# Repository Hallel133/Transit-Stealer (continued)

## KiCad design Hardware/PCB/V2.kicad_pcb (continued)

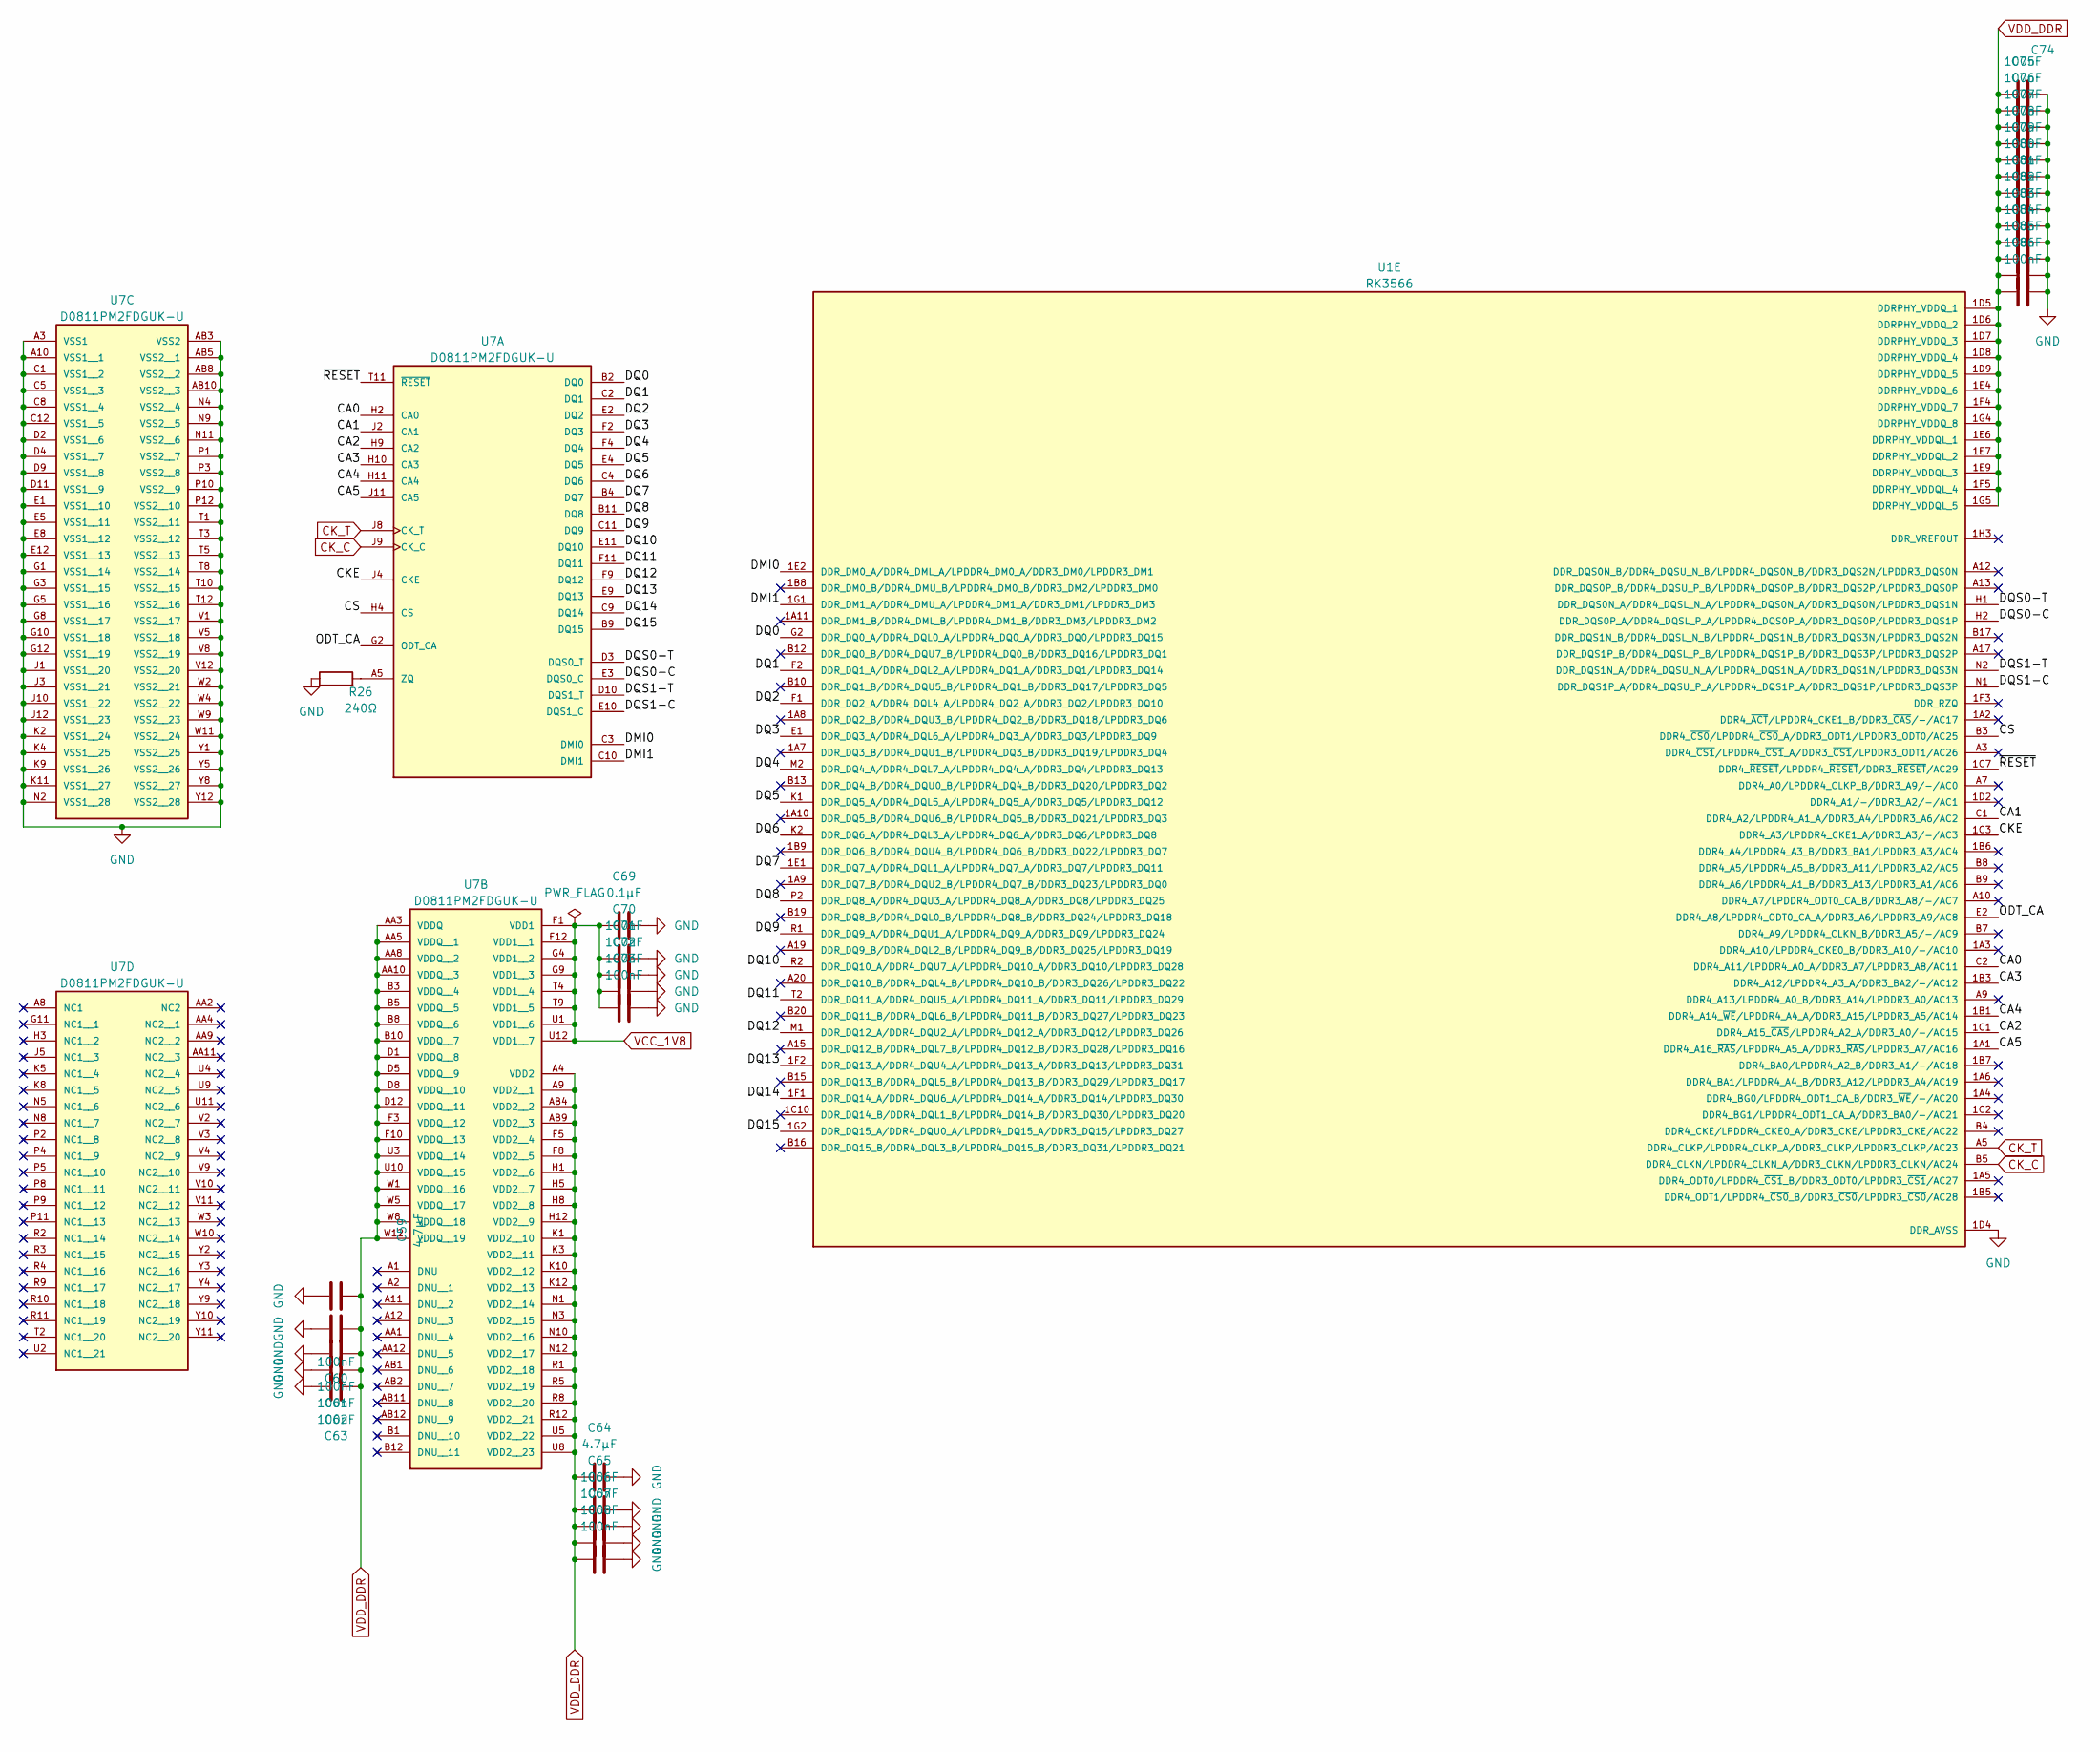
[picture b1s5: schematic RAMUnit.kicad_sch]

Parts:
C59, C64: 4.7µF; C_0402_1005Metric
C60, C61, C62, C63, C65, C66, C67, C68, C70, C71, C72, C73, C74, C75, C76, C77, C78, C79, C80, C81, C82, C83, C84, C85, C86: 100nF; C_0402_1005Metric
C69: 0.1µF; C_0402_1005Metric
R26: 240Ω; R_0402_1005Metric_Pad0.72x0.64mm_HandSolder
U1: RK3566; PARTREV 1.1
U7: D0811PM2FDGUK-U; PARTREV A00

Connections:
/LPDDR4/CA0: U1.C2 (DDR4_A11/LPDDR4_A0_A/DDR3_A7/LPDDR3_A8/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), U7.H2 (CA0)
/LPDDR4/CA1: U1.C1 (DDR4_A2/LPDDR4_A1_A/DDR3_A4/LPDDR3_A6/A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), U7.J2 (CA1)
/LPDDR4/CA2: U1.1C1 (DDR4_A15_~CAS/LPDDR4_A2_A/DDR3_A0/-/AC15), U7.H9 (CA2)
/LPDDR4/CA3: U1.1B3 (DDR4_A12/LPDDR4_A3_A/DDR3_BA2/-/AC12), U7.H10 (CA3)
/LPDDR4/CA4: U1.1B1 (DDR4_A14_~WE/LPDDR4_A4_A/DDR3_A15/LPDDR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), U7.H11 (CA4)
/LPDDR4/CA5: U1.1A1 (DDR4_A16_~RAS/LPDDR4_A5_A/DDR3_~RAS/LPD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), U7.J11 (CA5)
/LPDDR4/CKE: U1.1C3 (DDR4_A3/LPDDR4_CKE1_A/DDR3_A3/-/AC3), U7.J4 (CKE)
/LPDDR4/CS: U1.B3 (DDR4_~CS0/LPDDR4_~CS0_A/DDR3_ODT1/LPDDR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), U7.H4 (CS)
/LPDDR4/DMI0: U1.1E2 (DDR_DM0_A/DDR4_DML_A/LPDDR4_DM0_A/DDR3_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), U7.C3 (DMI0)
/LPDDR4/DMI1: U1.1G1 (DDR_DM1_A/DDR4_DMU_A/LPDDR4_DM1_A/DDR3_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), U7.C10 (DMI1)
/LPDDR4/DQ0: U1.G2 (DDR_DQ0_A/DDR4_DQL0_A/LPDDR4_DQ0_A/DDR3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), U7.B2 (DQ0)
/LPDDR4/DQ1: U1.F2 (DDR_DQ1_A/DDR4_DQL2_A/LPDDR4_DQ1_A/DDR3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), U7.C2 (DQ1)
/LPDDR4/DQ2: U1.F1 (DDR_DQ2_A/DDR4_DQL4_A/LPDDR4_DQ2_A/DDR3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), U7.E2 (DQ2)
/LPDDR4/DQ3: U1.E1 (DDR_DQ3_A/DDR4_DQL6_A/LPDDR4_DQ3_A/DDR3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), U7.F2 (DQ3)
/LPDDR4/DQ4: U1.M2 (DDR_DQ4_A/DDR4_DQL7_A/LPDDR4_DQ4_A/DDR3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), U7.F4 (DQ4)
/LPDDR4/DQ5: U1.K1 (DDR_DQ5_A/DDR4_DQL5_A/LPDDR4_DQ5_A/DDR3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), U7.E4 (DQ5)
/LPDDR4/DQ6: U1.K2 (DDR_DQ6_A/DDR4_DQL3_A/LPDDR4_DQ6_A/DDR3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), U7.C4 (DQ6)
/LPDDR4/DQ7: U1.1E1 (DDR_DQ7_A/DDR4_DQL1_A/LPDDR4_DQ7_A/DDR3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), U7.B4 (DQ7)
/LPDDR4/DQ8: U1.P2 (DDR_DQ8_A/DDR4_DQU3_A/LPDDR4_DQ8_A/DDR3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), U7.B11 (DQ8)
/LPDDR4/DQ9: U1.R1 (DDR_DQ9_A/DDR4_DQU1_A/LPDDR4_DQ9_A/DDR3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), U7.C11 (DQ9)
/LPDDR4/DQ10: U1.R2 (DDR_DQ10_A/DDR4_DQU7_A/LPDDR4_DQ10_A/DD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), U7.E11 (DQ10)
/LPDDR4/DQ11: U1.T2 (DDR_DQ11_A/DDR4_DQU5_A/LPDDR4_DQ11_A/DD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), U7.F11 (DQ11)
/LPDDR4/DQ12: U1.M1 (DDR_DQ12_A/DDR4_DQU2_A/LPDDR4_DQ12_A/DD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), U7.F9 (DQ12)
/LPDDR4/DQ13: U1.1F2 (DDR_DQ13_A/DDR4_DQU4_A/LPDDR4_DQ13_A/DD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), U7.E9 (DQ13)
/LPDDR4/DQ14: U1.1F1 (DDR_DQ14_A/DDR4_DQU6_A/LPDDR4_DQ14_A/DD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), U7.C9 (DQ14)
/LPDDR4/DQ15: U1.1G2 (DDR_DQ15_A/DDR4_DQU0_A/LPDDR4_DQ15_A/DD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), U7.B9 (DQ15)
/LPDDR4/DQS0-C: U1.H2 (DDR_DQS0P_A/DDR4_DQSL_P_A/LPDDR4_DQS0P_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), U7.E3 (DQS0_C)
/LPDDR4/DQS0-T: U1.H1 (DDR_DQS0N_A/DDR4_DQSL_N_A/LPDDR4_DQS0N_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), U7.D3 (DQS0_T)
/LPDDR4/DQS1-C: U1.N1 (DDR_DQS1P_A/DDR4_DQSU_P_A/LPDDR4_DQS1P_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), U7.E10 (DQS1_C)
/LPDDR4/DQS1-T: U1.N2 (DDR_DQS1N_A/DDR4_DQSU_N_A/LPDDR4_DQS1N_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), U7.D10 (DQS1_T)
/LPDDR4/ODT_CA: U1.E2 (DDR4_A8/LPDDR4_ODT0_CA_A/DDR3_A6/LPDDR3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), U7.G2 (ODT_CA)
/LPDDR4/~RESET: U1.1C7 (DDR4_~RESET/LPDDR4_~RESET/DDR3_~RESET/A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), U7.T11 (~RESET)
CK_C: U1.B5 (DDR4_CLKN/LPDDR4_CLKN_A/DDR3_CLKN/LPDDR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), U7.J9 (CK_C)
CK_T: U1.A5 (DDR4_CLKP/LPDDR4_CLKP_A/DDR3_CLKP/LPDDR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), U7.J8 (CK_T)
GND: C59.2, C60.2, C61.2, C62.2, C63.2, C64.2, C65.2, C66.2, C67.2, C68.2, C69.1, C70.2, C71.2, C72.2, C73.2, C74.2, C75.2, C76.2, C77.2, C78.2, C79.2, C80.2, C81.2, C82.2, C83.2, C84.2, C85.2, C86.2, R26.1, U1.1D4 (DDR_AVSS), U7.A3 (VSS1), U7.A10 (VSS1__1), U7.AB3 (VSS2), U7.AB5 (VSS2__1), U7.AB8 (VSS2__2), U7.AB10 (VSS2__3), U7.C1 (VSS1__2), U7.C5 (VSS1__3), U7.C8 (VSS1__4), U7.C12 (VSS1__5), U7.D2 (VSS1__6), U7.D4 (VSS1__7), U7.D9 (VSS1__8), U7.D11 (VSS1__9), U7.E1 (VSS1__10), U7.E5 (VSS1__11), U7.E8 (VSS1__12), U7.E12 (VSS1__13), U7.G1 (VSS1__14), U7.G3 (VSS1__15), U7.G5 (VSS1__16), U7.G8 (VSS1__17), U7.G10 (VSS1__18), U7.G12 (VSS1__19), U7.J1 (VSS1__20), U7.J3 (VSS1__21), U7.J10 (VSS1__22), U7.J12 (VSS1__23), U7.K2 (VSS1__24), U7.K4 (VSS1__25), U7.K9 (VSS1__26), U7.K11 (VSS1__27), U7.N2 (VSS1__28), U7.N4 (VSS2__4), U7.N9 (VSS2__5), U7.N11 (VSS2__6), U7.P1 (VSS2__7), U7.P3 (VSS2__8), U7.P10 (VSS2__9), U7.P12 (VSS2__10), U7.T1 (VSS2__11), U7.T3 (VSS2__12), U7.T5 (VSS2__13), U7.T8 (VSS2__14), U7.T10 (VSS2__15), U7.T12 (VSS2__16), U7.V1 (VSS2__17), U7.V5 (VSS2__18), U7.V8 (VSS2__19), U7.V12 (VSS2__20), U7.W2 (VSS2__21), U7.W4 (VSS2__22), U7.W9 (VSS2__23), U7.W11 (VSS2__24), U7.Y1 (VSS2__25), U7.Y5 (VSS2__26), U7.Y8 (VSS2__27), U7.Y12 (VSS2__28); also elsewhere on the board
unnamed: R26.2, U7.A5 (ZQ)
VCC_1V8: C69.2, C70.1, C71.1, C72.1, C73.1, U7.F1 (VDD1), U7.F12 (VDD1__1), U7.G4 (VDD1__2), U7.G9 (VDD1__3), U7.T4 (VDD1__4), U7.T9 (VDD1__5), U7.U1 (VDD1__6), U7.U12 (VDD1__7); also elsewhere on the board
VDD_DDR: C59.1, C60.1, C61.1, C62.1, C63.1, C64.1, C65.1, C66.1, C67.1, C68.1, C74.1, C75.1, C76.1, C77.1, C78.1, C79.1, C80.1, C81.1, C82.1, C83.1, C84.1, C85.1, C86.1, U1.1D5 (DDRPHY_VDDQ_1), U1.1D6 (DDRPHY_VDDQ_2), U1.1D7 (DDRPHY_VDDQ_3), U1.1D8 (DDRPHY_VDDQ_4), U1.1D9 (DDRPHY_VDDQ_5), U1.1E4 (DDRPHY_VDDQ_6), U1.1E6 (DDRPHY_VDDQL_1), U1.1E7 (DDRPHY_VDDQL_2), U1.1E9 (DDRPHY_VDDQL_3), U1.1F4 (DDRPHY_VDDQ_7), U1.1F5 (DDRPHY_VDDQL_4), U1.1G4 (DDRPHY_VDDQ_8), U1.1G5 (DDRPHY_VDDQL_5), U7.A4 (VDD2), U7.A9 (VDD2__1), U7.AA3 (VDDQ), U7.AA5 (VDDQ__1), U7.AA8 (VDDQ__2), U7.AA10 (VDDQ__3), U7.AB4 (VDD2__2), U7.AB9 (VDD2__3), U7.B3 (VDDQ__4), U7.B5 (VDDQ__5), U7.B8 (VDDQ__6), U7.B10 (VDDQ__7), U7.D1 (VDDQ__8), U7.D5 (VDDQ__9), U7.D8 (VDDQ__10), U7.D12 (VDDQ__11), U7.F3 (VDDQ__12), U7.F5 (VDD2__4), U7.F8 (VDD2__5), U7.F10 (VDDQ__13), U7.H1 (VDD2__6), U7.H5 (VDD2__7), U7.H8 (VDD2__8), U7.H12 (VDD2__9), U7.K1 (VDD2__10), U7.K3 (VDD2__11), U7.K10 (VDD2__12), U7.K12 (VDD2__13), U7.N1 (VDD2__14), U7.N3 (VDD2__15), U7.N10 (VDD2__16), U7.N12 (VDD2__17), U7.R1 (VDD2__18), U7.R5 (VDD2__19), U7.R8 (VDD2__20), U7.R12 (VDD2__21), U7.U3 (VDDQ__14), U7.U5 (VDD2__22), U7.U8 (VDD2__23), U7.U10 (VDDQ__15), U7.W1 (VDDQ__16), U7.W5 (VDDQ__17), U7.W8 (VDDQ__18), U7.W12 (VDDQ__19); also elsewhere on the board

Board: 8 copper layers, 158 parts (35 on the bottom side), 163 nets, no tracks yet.

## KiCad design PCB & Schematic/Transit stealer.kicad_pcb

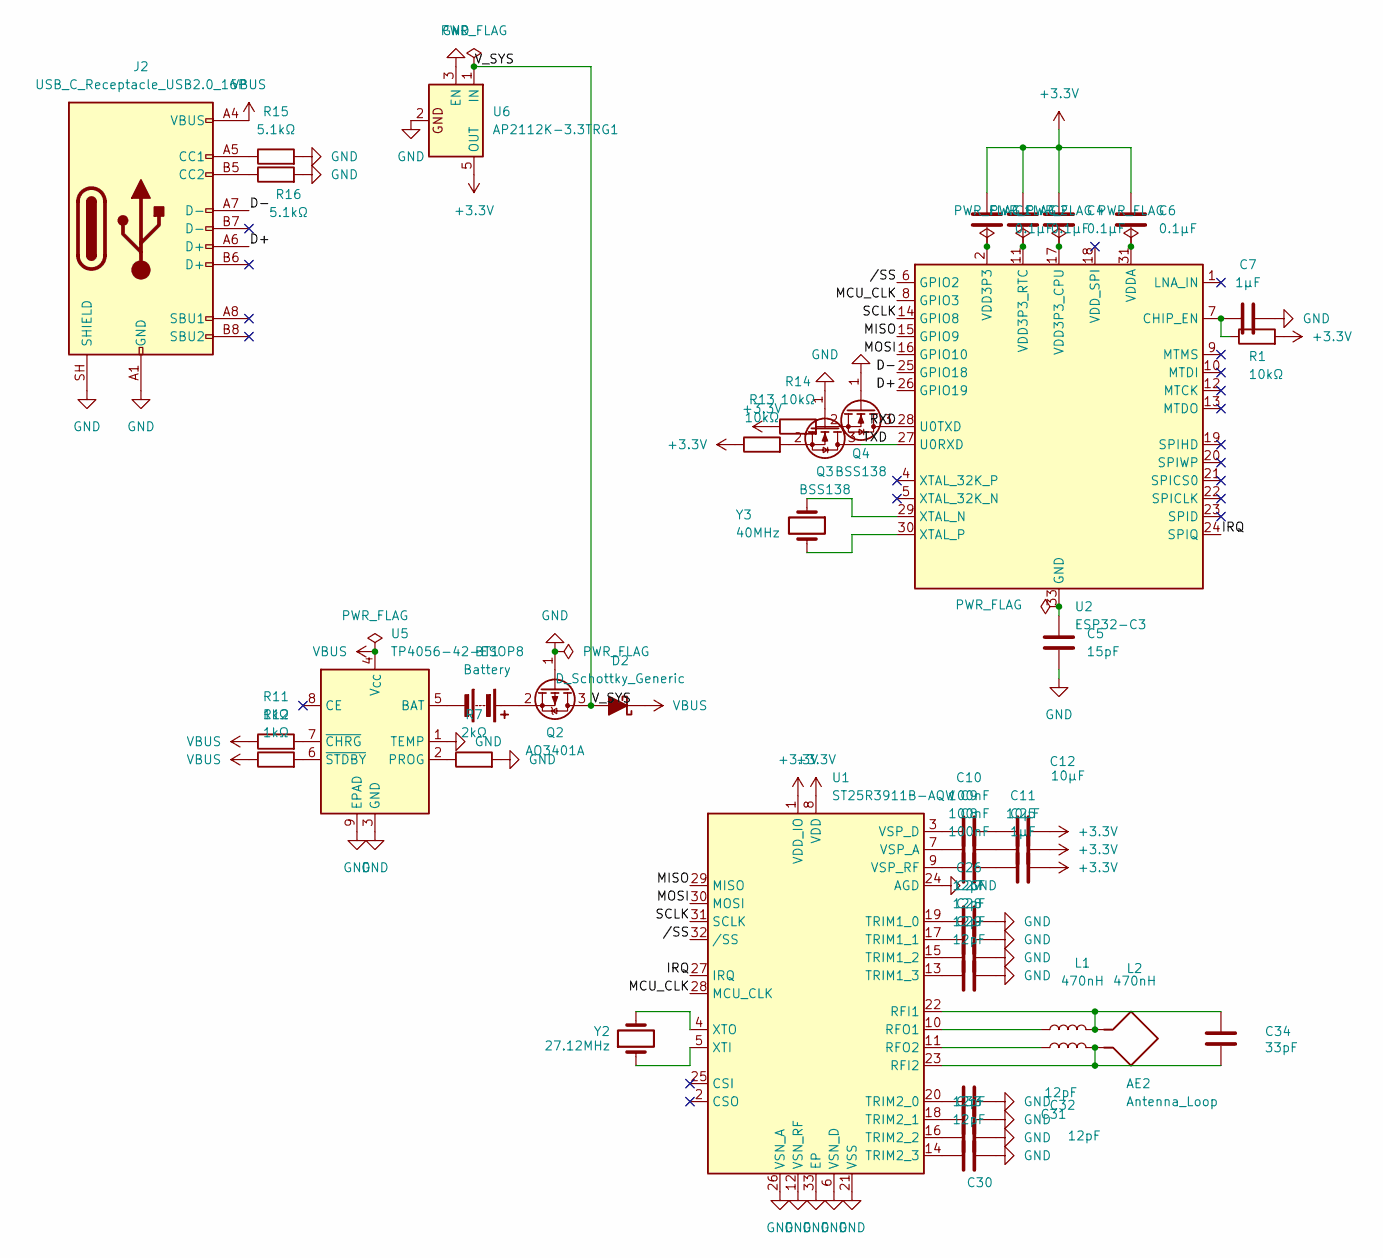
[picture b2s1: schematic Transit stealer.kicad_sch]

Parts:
AE2: Antenna_Loop; NFC Antenna
BT1: Battery; SolderWire-0.127sqmm_1x02_P3.7mm_D0.48mm_OD1mm
C1, C2, C4, C6: 0.1μF; C_0402_1005Metric
C5: 15pF; C_0603_1608Metric_Pad1.08x0.95mm_HandSolder
C7: 1μF; C_0402_1005Metric
C8, C9, C10: 100nF; C_0402_1005Metric
C11, C12: 10µF; C_0603_1608Metric
C25: 1µF; C_0402_1005Metric
C26, C27, C28, C29, C30, C31, C32, C33: 12pF; C_0201_0603Metric
C34: 33pF; C_0201_0603Metric
D2: D_Schottky_Generic; D_SOD-123
J2: USB_C_Receptacle_USB2.0_16P; USB_C_Receptacle_GCT_USB4105-xx-A_16P_TopMnt_Horizontal
L1, L2: 470nH; lnductor 470nH
Q2: AO3401A; SOT-23
Q3, Q4: BSS138; SOT-23
R1, R13, R14: 10kΩ; R_0402_1005Metric_Pad0.72x0.64mm_HandSolder
R7: 2kΩ; R_0402_1005Metric
R11, R12: 1kΩ; R_0402_1005Metric
R15, R16: 5.1kΩ; R_0402_1005Metric
U1: ST25R3911B-AQW; VQFN-32-1EP_5x5mm_P0.5mm_EP3.5x3.5mm_ThermalVias
U2: ESP32-C3; QFN-32-1EP_5x5mm_P0.5mm_EP3.7x3.7mm
U5: TP4056-42-ESOP8; SOIC-8-1EP_3.9x4.9mm_P1.27mm_EP2.41x3.3mm_ThermalVias
U6: AP2112K-3.3TRG1; SOT-23-5
Y2: 27.12MHz; Crystal_SMD_3225-4Pin_3.2x2.5mm
Y3: 40MHz; Crystal_SMD_3225-4Pin_3.2x2.5mm

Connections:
+3.3V: C1.1, C2.1, C4.1, C6.1, C11.2, C12.2, C25.1, R1.2, R13.1, R14.1, U1.1 (VDD_IO), U1.8 (VDD), U6.5 (OUT)
/D+: J2.A6 (D+), U2.26 (GPIO19)
/D-: J2.A7 (D-), U2.25 (GPIO18)
/IRQ: U1.27 (IRQ), U2.24 (SPIQ)
/MCU_CLK: U1.28 (MCU_CLK), U2.8 (GPIO3)
/MISO: U1.29 (MISO), U2.15 (GPIO9)
/MOSI: U1.30 (MOSI), U2.16 (GPIO10)
/RXD: Q4.3 (D), U2.28 (U0TXD)
/SCLK: U1.31 (SCLK), U2.14 (GPIO8)
/TXD: Q3.3 (D), U2.27 (U0RXD)
/V_SYS: D2.2 (A), Q2.3 (D), U6.1 (IN)
//SS: U1.32 (/SS), U2.6 (GPIO2)
GND: C5.2, C7.2, C26.1, C27.1, C28.1, C29.1, C30.1, C31.1, C32.1, C33.1, J2.A1 (GND), J2.A12 (GND), J2.B1 (GND), J2.B12 (GND), J2.SH (SHIELD), Q2.1 (G), Q3.1 (G), Q4.1 (G), R7.2, R15.2, R16.2, U1.6 (VSN_D), U1.12 (VSN_RF), U1.21 (VSS), U1.24 (AGD), U1.26 (VSN_A), U1.33 (EP), U5.1 (TEMP), U5.3 (GND), U5.9 (EPAD), U6.2, U6.3 (EN)
unnamed: BT1.1 (+), Q2.2 (S)
unnamed: BT1.2 (-), U5.5 (BAT)
unnamed: C1.2, U2.2 (VDD3P3), U2.3 (VDD3P3)
unnamed: C6.2, U2.31 (VDDA), U2.32 (VDDA)
unnamed: C10.2, C12.1
unnamed: C9.2, C11.1
unnamed: C8.2, C25.2
unnamed: J2.A5 (CC1), R15.1
unnamed: J2.B5 (CC2), R16.1
unnamed: Q3.2 (S), R13.2
unnamed: Q4.2 (S), R14.2
unnamed 24: AE2.1, C34.1, L1.2, U1.22 (RFI1); also elsewhere on the board
unnamed 25: AE2.2, C34.2, L2.2, U1.23 (RFI2); also elsewhere on the board
unnamed: L1.1, U1.10 (RFO1)
unnamed: L2.1, U1.11 (RFO2)
unnamed: C26.2, U1.19 (TRIM1_0)
unnamed: C27.2, U1.17 (TRIM1_1)
unnamed: C28.2, U1.15 (TRIM1_2)
unnamed: C29.2, U1.13 (TRIM1_3)
unnamed: C30.2, U1.20 (TRIM2_0)
unnamed: C31.2, U1.18 (TRIM2_1)
unnamed: C32.2, U1.16 (TRIM2_2)
unnamed: C33.2, U1.14 (TRIM2_3)
unnamed: C9.1, U1.7 (VSP_A)
unnamed: C10.1, U1.3 (VSP_D)
unnamed: C8.1, U1.9 (VSP_RF)
unnamed: U1.5 (XTI), Y2.1
unnamed: U1.4 (XTO), Y2.2
unnamed: C7.1, R1.1, U2.7 (CHIP_EN)
unnamed: C5.1, U2.33 (GND)
unnamed: C4.2, U2.17 (VDD3P3_CPU)
unnamed: C2.2, U2.11 (VDD3P3_RTC)
unnamed: U2.29 (XTAL_N), Y3.1
unnamed: U2.30 (XTAL_P), Y3.2
unnamed: R7.1, U5.2 (PROG)
unnamed: R11.2, U5.7 (~CHRG)
unnamed: R12.2, U5.6 (~STDBY)
VBUS: D2.1 (K), J2.A4 (VBUS), J2.A9 (VBUS), J2.B4 (VBUS), J2.B9 (VBUS), R11.1, R12.1, U5.4 (V_{CC})

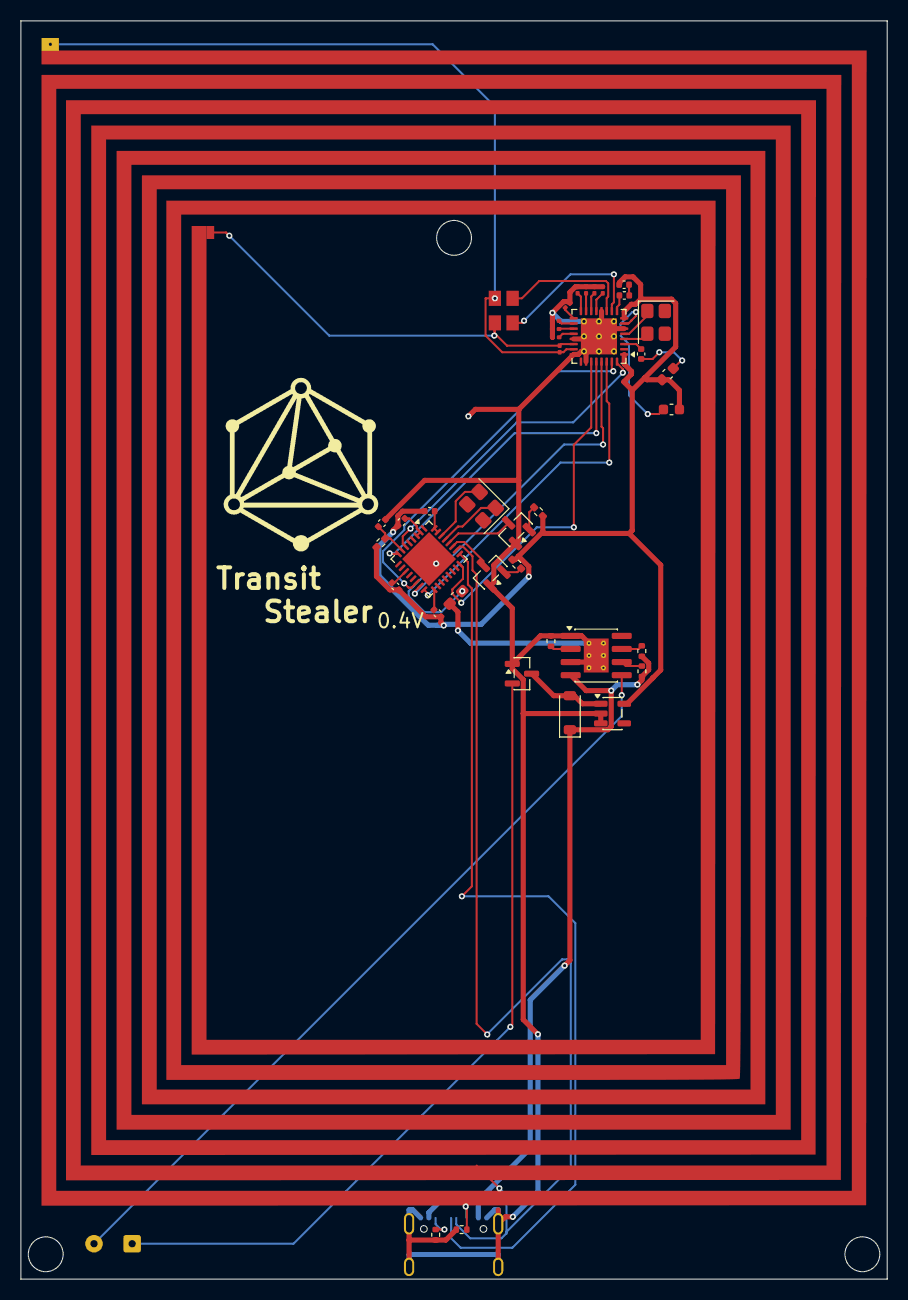
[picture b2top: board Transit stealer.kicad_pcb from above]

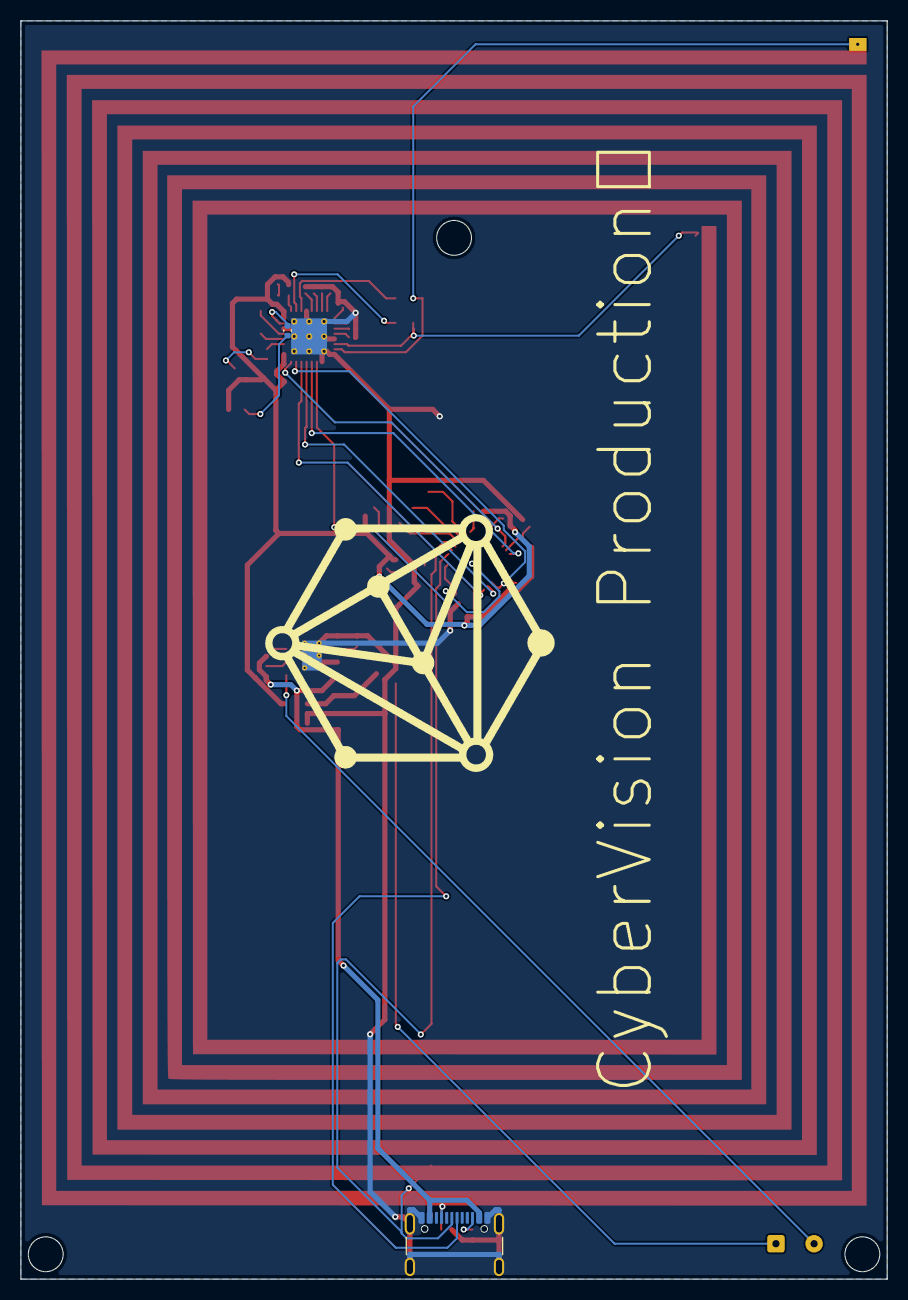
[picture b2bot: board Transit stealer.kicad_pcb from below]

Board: 2 copper layers, 84.0 x 122.0 mm, 45 parts (3 on the bottom side), 51 nets.

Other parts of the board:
Antena: Antena; NFC Antenna
g: LOGO

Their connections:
unnamed 24: Antena.1; also elsewhere on the board
unnamed 25: Antena.2; also elsewhere on the board

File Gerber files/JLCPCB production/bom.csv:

Designator,Footprint,Quantity,Value,LCSC Part #
ANTENA,NFC Antenna ,1,Antena,
BT1,SolderWire-0.127sqmm_1x02_P3.7mm_D0.48mm_OD1mm,1,Battery,
"C1, C2, C4, C6",0402,4,0.1μF,
"C10, C8, C9",0402,3,100nF,
"C11, C12",0603,2,10µF,
"C25, C7",0402,2,1µF,
"C26, C27, C28, C29, C30, C31, C32, C33",0201,8,12pF,
C34,0201,1,33pF,
C5,0603,1,15pF,
D2,D_SOD-123,1,D_Schottky_Generic,
J2,USB_C_Receptacle_GCT_USB4105-xx-A_16P_TopMnt_Horizontal,1,USB_C_Receptacle_USB2.0_16P,
"L1, L2",lnductor 470nH,2,470nH,
Q2,SOT-23,1,AO3401A,
"Q3, Q4",SOT-23,2,BSS138,
"R1, R13, R14",0402,3,10kΩ,
"R11, R12",0402,2,1kΩ,
"R15, R16",0402,2,5.1kΩ,
R7,0402,1,2kΩ,
U1,VQFN-32-1EP_5x5mm_P0.5mm_EP3.5x3.5mm_ThermalVias,1,ST25R3911B-AQW,
U2,QFN-32-1EP_5x5mm_P0.5mm_EP3.7x3.7mm,1,ESP32-C3,
U5,SOIC-8-1EP_3.9x4.9mm_P1.27mm_EP2.41x3.3mm_ThermalVias,1,TP4056-42-ESOP8,
U6,SOT-23-5,1,AP2112K-3.3TRG1,
Y2,Crystal_SMD_3225-4Pin_3.2x2.5mm,1,27.12MHz,
Y3,Crystal_SMD_3225-4Pin_3.2x2.5mm,1,40MHz,
